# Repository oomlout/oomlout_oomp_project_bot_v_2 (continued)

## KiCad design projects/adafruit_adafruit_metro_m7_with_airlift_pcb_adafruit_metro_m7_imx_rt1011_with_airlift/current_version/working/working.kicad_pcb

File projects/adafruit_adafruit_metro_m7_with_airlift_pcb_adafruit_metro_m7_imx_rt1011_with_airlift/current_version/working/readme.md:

# adafruit_metro_m7_with_airlift_pcb
 
## summary 
* id: adafruit_adafruit_metro_m7_with_airlift_pcb_adafruit_metro_m7_imx_rt1011_with_airlift
* user: adafruit
* name: adafruit_metro_m7_with_airlift_pcb
* board: adafruit_metro_m7_imx_rt1011_with_airlift
* repo: https://github.com/adafruit/Adafruit-Metro-M7-with-AirLift-PCB

* src_file_repo_sch: 
* src_file_repo_sch_link: https://github.com/adafruit/Adafruit-Metro-M7-with-AirLift-PCB/tree/main/
* full details link: https://github.com/oomlout/oomlout_oomp_project_bot_v_2/tree/main/projects/adafruit_adafruit_metro_m7_with_airlift_pcb_adafruit_metro_m7_imx_rt1011_with_airlift/current_version/working  

## schematic  
  
[schematic (pdf)](working_schematic.pdf) 

## pcb  

[board (pdf)](working.pdf)  

## working_bom
| Id | Designator | Footprint | Quantity | Designation | Supplier and ref |  | None | 
| --- | --- | --- | --- | --- | --- | --- | --- | 
| 1 | U$18 | METROM7_RT1011AIR_TOP | 1 |  |  |  | [''] | 
| 2 | R5,R13,R7,R12,R15,R9,R10 | 0603-NO | 7 | 10K |  |  | [''] | 
| 3 | R11,R17,R8,R3,R14,R2 | 0603-NO | 6 | 5.1K |  |  | [''] | 
| 4 | X2 | 2X05_1.27MM_BOX_POSTS | 1 | 2x5 0.05 SWD" |  |  | [''] | 
| 5 | C46,C40,C47,C21,C39,C19,C31,C20,C2,C55,C18,C51,C3,C5,C48,C45 | 0805-NO | 16 | 10uF |  |  | [''] | 
| 6 | D1 | SOD-123 | 1 | MBR120 |  |  | [''] | 
| 7 | C58,C33,C50,C53,C57,C52,C38,C56,C49 | 0603-NO | 9 | 0.22uF |  |  | [''] | 
| 8 | U3 | SOIC8_208MIL | 1 | W25Q64JV |  |  | [''] | 
| 9 | TR1,T2 | SOT-23 | 2 | DMP3098L-7 |  |  | [''] | 
| 10 | FD2,FD3,FD1 | FIDUCIAL_1MM | 3 | FIDUCIAL_1MM |  |  | [''] | 
| 11 | @HOLE3,@HOLE0,@HOLE1,@HOLE2 |  | 4 |  |  |  | [''] | 
| 12 | JP1 | 1X01_ROUND | 1 |  |  |  | [''] | 
| 13 | IC4 | SOT23-WIDE | 1 | RESET_SUPERVISORAPX80X_SA |  |  | [''] | 
| 14 | C26,C25 | 0603-NO | 2 | 16pF |  |  | [''] | 
| 15 | LED1 | LED3535_FULLPADS | 1 | WS2812B_3535FULL |  |  | [''] | 
| 16 | C34 | 0805-NO | 1 | 22uF |  |  | [''] | 
| 17 | PC1,PC2 | PANASONIC_D | 2 | 47uF/25V |  |  | [''] | 
| 18 | IC1 | SOT23-5L | 1 | 74AHC1G125 |  |  | [''] | 
| 19 | C6,C12,C37,C13,C35,C41,C43,C22,C32,C7 | 0603-NO | 10 | 0.1uF |  |  | [''] | 
| 20 | U$11 | PCBFEAT-REV-040 | 1 |  |  |  | [''] | 
| 21 | R16,R1 | 0603-NO | 2 | 100K |  |  | [''] | 
| 22 | R4 | 0603-NO | 1 | 2.2M |  |  | [''] | 
| 23 | C30,C54,C36,C42,C44,C29 | 0603-NO | 6 | 1uF |  |  | [''] | 
| 24 | POWER0,IOL0 | 1X08_OVALWAVE | 2 | 1x8F |  |  | [''] | 
| 25 | L2 | INDUCTOR_1007 | 1 | 4.7uH |  |  | [''] | 
| 26 | Y1 | CRYSTAL_2.5X2 | 1 | 24MHz 10pF |  |  | [''] | 
| 27 | IOH0 | 1X10_OVALWAVE | 1 | 1x10F |  |  | [''] | 
| 28 | X5 | DCJACK_2MM_PTH | 1 | 2.1mm |  |  | [''] | 
| 29 | R6 | 0603-NO | 1 | 30K |  |  | [''] | 
| 30 | U1 | SOT223-R | 1 | NCP1117ST50T3G |  |  | [''] | 
| 31 | RESET0 | EVQ-Q2_SMALLER | 1 | 6x6mm |  |  | [''] | 
| 32 | L0 | CHIPLED_0603_NOOUTLINE | 1 | RED |  |  | [''] | 
| 33 | X4 | USB_C_CUSB31-CFM2AX-01-X | 1 | USB C |  |  | [''] | 
| 34 | ICSP0 | 2X03_ROUND_70MIL | 1 | 2x3M |  |  | [''] | 
| 35 | ECC1 | SOIC8 | 1 | ATECC108 |  |  | [''] | 
| 36 | AD0 | 1X06_OVALWAVE | 1 | 1x6F |  |  | [''] | 
| 37 | F2 | R1206 | 1 | FUSE |  |  | [''] | 
| 38 | ON0 | CHIPLED_0603_NOOUTLINE | 1 | GREEN |  |  | [''] | 
| 39 | U2 | SOT23-DBV | 1 | AP2112K-3.3 |  |  | [''] | 
| 40 | CONN1 | JST_SH4 | 1 | STEMMA_I2C_QT |  |  | [''] | 
| 41 | X6 | WROOM32 | 1 | ESP32_WROOM32 |  |  | [''] | 
| 42 | SW2 | DIPSWITCH_2PIN | 1 | DIP2 |  |  | [''] | 
| 43 | IC2 | QFP50P1400X1400X160-80N | 1 | IMX_RT1010 |  |  | [''] | 
| 44 | SW1 | SPDT_SMT_SSSS811101 | 1 | SPDT_RA |  |  | [''] | 
| 45 | U$12 | METROM7_RT1011AIR_BOT | 1 |  |  |  | [''] | 
| 46 | TP2,TP1 | TESTPOINT_ROUND_1.5MM | 2 |  |  |  | [''] | 

## bom_schematic
| Ref | Qnty | Value | Cmp name | Footprint | Description | Vendor | DNP | 
| --- | --- | --- | --- | --- | --- | --- | --- | 
| AD0 | 1 | 1x6F | HEADER-1X6OVALWAVE | working:1X06_OVALWAVE |  |  |  | 
| C2, C3, C5, C18, C19, C20, C21, C31, C39, C40, C45, C46, C47, C48, C51, C55 | 16 | 10uF | CAP_CERAMIC0805-NOOUTLINE | working:0805-NO |  |  |  | 
| C6, C7, C12, C13, C22, C32, C35, C37, C41, C43 | 10 | 0.1uF | CAP_CERAMIC0603_NO | working:0603-NO |  |  |  | 
| C25, C26 | 2 | 16pF | CAP_CERAMIC0603_NO | working:0603-NO |  |  |  | 
| C29, C30, C36, C42, C44, C54 | 6 | 1uF | CAP_CERAMIC0603_NO | working:0603-NO |  |  |  | 
| C33, C38, C49, C50, C52, C53, C56, C57, C58 | 9 | 0.22uF | CAP_CERAMIC0603_NO | working:0603-NO |  |  |  | 
| C34 | 1 | 22uF | CAP_CERAMIC0805-NOOUTLINE | working:0805-NO |  |  |  | 
| CONN1 | 1 | STEMMA_I2C_QT | STEMMA_I2C_QT | working:JST_SH4 |  |  |  | 
| D1 | 1 | MBR120 | DIODE-SCHOTTKYSOD-123 | working:SOD-123 |  |  |  | 
| ECC1 | 1 | ATECC108 | ATECC108 | working:SOIC8 |  |  |  | 
| F2 | 1 | FUSE | PTCFUSE-1206 | working:R1206 |  |  |  | 
| FD1, FD2, FD3 | 3 | FIDUCIAL_1MM | FIDUCIAL_1MM | working:FIDUCIAL_1MM |  |  |  | 
| IC1 | 1 | 74AHC1G125 | 74AHC1G125 | working:SOT23-5L |  |  |  | 
| IC2 | 1 | IMX_RT1010 | IMX_RT1010 | working:QFP50P1400X1400X160-80N |  |  |  | 
| IC4 | 1 | RESET_SUPERVISORAPX80X_SA | RESET_SUPERVISORAPX80X_SA | working:SOT23-WIDE |  |  |  | 
| ICSP0 | 1 | 2x3M | HEADER-2X3 | working:2X03_ROUND_70MIL |  |  |  | 
| IOH0 | 1 | 1x10F | HEADER-1X10OVALWAVE | working:1X10_OVALWAVE |  |  |  | 
| IOL0 | 1 | 1x8F | HEADER-1X8OVALWAVE | working:1X08_OVALWAVE |  |  |  | 
| JP1 | 1 | HEADER-1X1ROUND | HEADER-1X1ROUND | working:1X01_ROUND |  |  |  | 
| L0 | 1 | RED | LED0603_NOOUTLINE | working:CHIPLED_0603_NOOUTLINE |  |  |  | 
| L2 | 1 | 4.7uH | INDUCTOR | working:INDUCTOR_1007 |  |  |  | 
| LED1 | 1 | WS2812B_3535FULL | WS2812B_3535FULL | working:LED3535_FULLPADS |  |  |  | 
| ON0 | 1 | GREEN | LED0603_NOOUTLINE | working:CHIPLED_0603_NOOUTLINE |  |  |  | 
| PC1, PC2 | 2 | 47uF/25V | CAP_ELECTROLYTICPANASONIC_D | working:PANASONIC_D |  |  |  | 
| POWER0 | 1 | 1x8F | HEADER-1X8OVALWAVE | working:1X08_OVALWAVE |  |  |  | 
| R1, R16 | 2 | 100K | RESISTOR_0603_NOOUT | working:0603-NO |  |  |  | 
| R2, R3, R8, R11, R14, R17 | 6 | 5.1K | RESISTOR_0603_NOOUT | working:0603-NO |  |  |  | 
| R4 | 1 | 2.2M | RESISTOR_0603_NOOUT | working:0603-NO |  |  |  | 
| R5, R7, R9, R10, R12, R13, R15 | 7 | 10K | RESISTOR_0603_NOOUT | working:0603-NO |  |  |  | 
| R6 | 1 | 30K | RESISTOR_0603_NOOUT | working:0603-NO |  |  |  | 
| RESET0 | 1 | 6x6mm | SWITCH_TACT_SMT_EVQQ2_SMALL | working:EVQ-Q2_SMALLER |  |  |  | 
| SW1 | 1 | SPDT_RA | SWITCH_SPDT | working:SPDT_SMT_SSSS811101 |  |  |  | 
| SW2 | 1 | DIP2 | DIPSWITCH_2PIN | working:DIPSWITCH_2PIN |  |  |  | 
| T2 | 1 | DMP3098L-7 | PMOSSOT23 | working:SOT-23 |  |  |  | 
| TP1, TP2 | 2 | TESTPOINTROUND1.5MM | TESTPOINTROUND1.5MM | working:TESTPOINT_ROUND_1.5MM |  |  |  | 
| TR1 | 1 | DMP3098L-7 | 0297_PMV48XP | working:SOT-23 |  |  |  | 
| U1 | 1 | NCP1117ST50T3G | LM1117SOT223-REFLOW | working:SOT223-R |  |  |  | 
| U2 | 1 | LP2985-XXDBVR | LP2985-XXDBVR | working:SOT23-DBV |  |  |  | 
| U3 | 1 | W25Q64JV | SPIFLASH_8PIN208MIL | working:SOIC8_208MIL |  |  |  | 
| X2 | 1 | 2x5 0.05" SWD | JTAG-CORTEXBOXPOSTS | working:2X05_1.27MM_BOX_POSTS |  |  |  | 
| X4 | 1 | USB C | USB_C | working:USB_C_CUSB31-CFM2AX-01-X |  |  |  | 
| X5 | 1 | 2.1mm | DCBARRELPTH | working:DCJACK_2MM_PTH |  |  |  | 
| X6 | 1 | ESP32_WROOM32 | ESP32_WROOM32 | working:WROOM32 |  |  |  | 
| Y1 | 1 | 24MHz 10pF | CRYSTAL2.5X2.0 | working:CRYSTAL_2.5X2 |  |  |  |

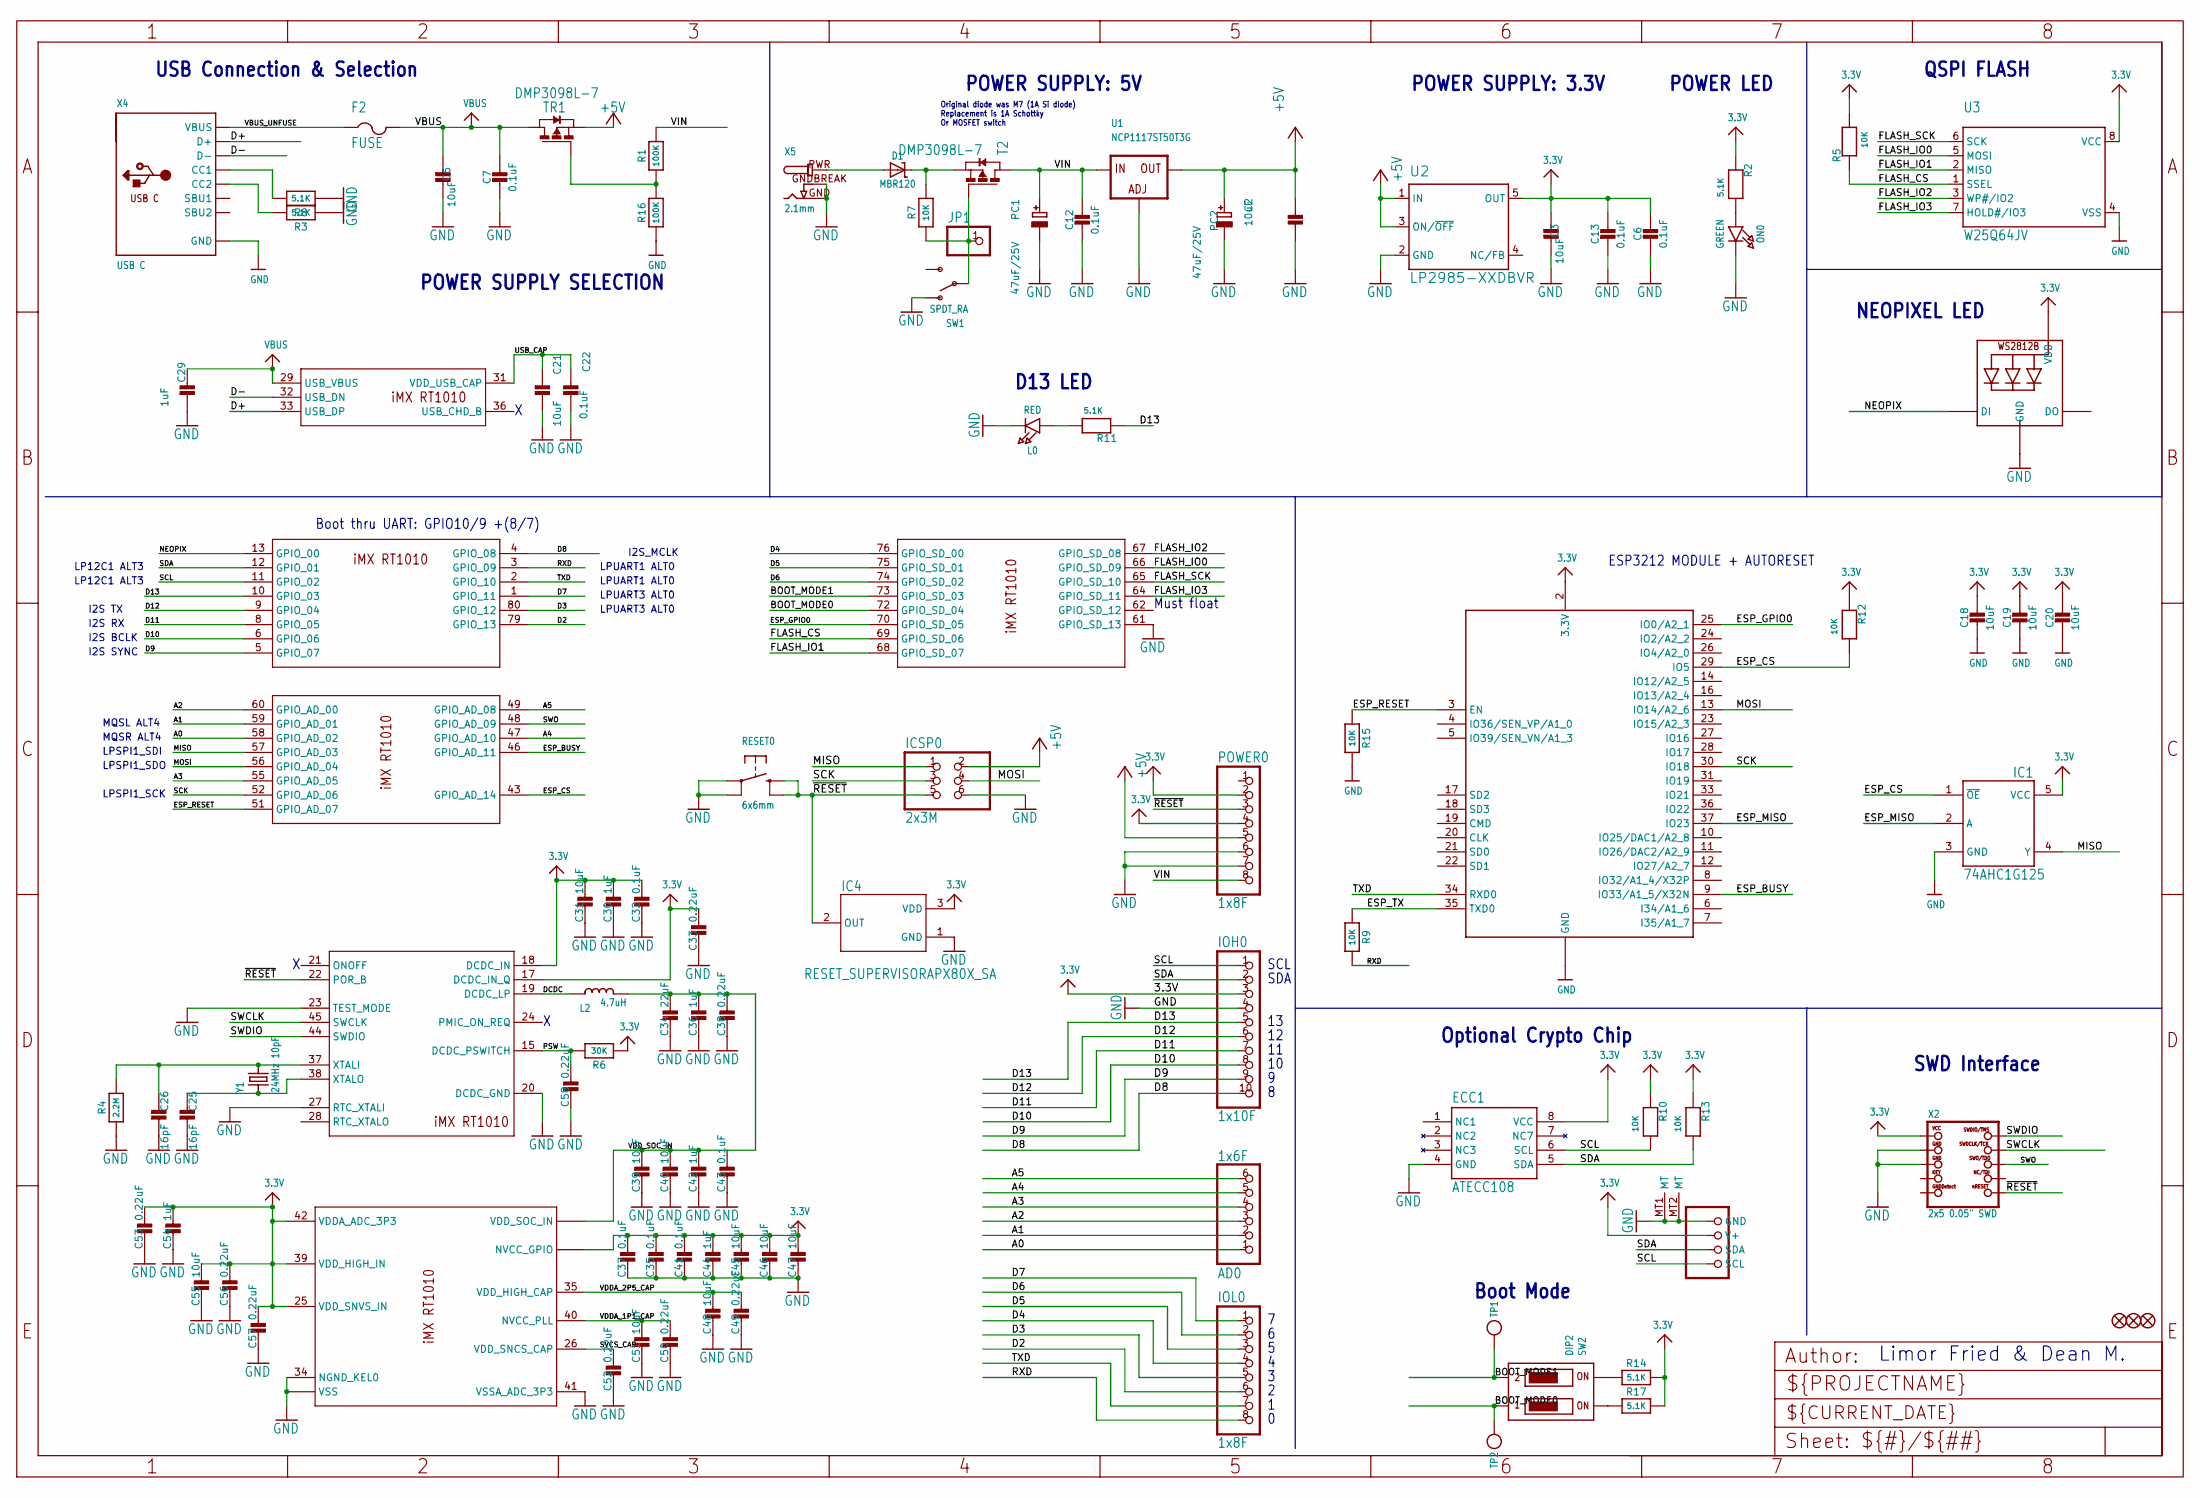
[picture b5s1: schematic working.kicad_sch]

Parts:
AD0: 1x6F; 1X06_OVALWAVE
C2, C3, C5, C18, C19, C20, C21, C31, C39, C40, C45, C46, C47, C48, C51, C55: 10uF; 0805-NO
C6, C7, C12, C13, C22, C32, C35, C37, C41, C43: 0.1uF; 0603-NO
C25, C26: 16pF; 0603-NO
C29, C30, C36, C42, C44, C54: 1uF; 0603-NO
C33, C38, C49, C50, C52, C53, C56, C57, C58: 0.22uF; 0603-NO
C34: 22uF; 0805-NO
CONN1: STEMMA_I2C_QT; JST_SH4
D1: MBR120; SOD-123
ECC1: ATECC108; SOIC8
F2: FUSE; R1206
FD1, FD2, FD3: FIDUCIAL_1MM
IC1: 74AHC1G125; SOT23-5L
IC2: IMX_RT1010; QFP50P1400X1400X160-80N
IC4: RESET_SUPERVISORAPX80X_SA; SOT23-WIDE
ICSP0: 2x3M; 2X03_ROUND_70MIL
IOH0: 1x10F; 1X10_OVALWAVE
IOL0: 1x8F; 1X08_OVALWAVE
JP1: HEADER-1X1ROUND; 1X01_ROUND
L0: RED; CHIPLED_0603_NOOUTLINE
L2: 4.7uH; INDUCTOR_1007
LED1: WS2812B_3535FULL; LED3535_FULLPADS
ON0: GREEN; CHIPLED_0603_NOOUTLINE
PC1, PC2: 47uF/25V; PANASONIC_D
POWER0: 1x8F; 1X08_OVALWAVE
R1, R16: 100K; 0603-NO
R2, R3, R8, R11, R14, R17: 5.1K; 0603-NO
R4: 2.2M; 0603-NO
R5, R7, R9, R10, R12, R13, R15: 10K; 0603-NO
R6: 30K; 0603-NO
RESET0: 6x6mm; EVQ-Q2_SMALLER
SW1: SPDT_RA; SPDT_SMT_SSSS811101
SW2: DIP2; DIPSWITCH_2PIN
T2: DMP3098L-7; SOT-23
TP1, TP2: TESTPOINTROUND1.5MM; TESTPOINT_ROUND_1.5MM
TR1: DMP3098L-7; SOT-23
U1: NCP1117ST50T3G; SOT223-R
U2: LP2985-XXDBVR; SOT23-DBV
U3: W25Q64JV; SOIC8_208MIL
X2: 2x5 0.05" SWD; 2X05_1.27MM_BOX_POSTS
X4: USB C; USB_C_CUSB31-CFM2AX-01-X
X5: 2.1mm; DCJACK_2MM_PTH
X6: ESP32_WROOM32; WROOM32
Y1: 24MHz 10pF; CRYSTAL_2.5X2

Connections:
3.3V: C3.2, C6.2, C13.1, C18.1, C19.1, C20.1, C30.1, C31.1, C32.1, C33.1, C35.1, C37.1, C41.1, C44.1, C45.1, C46.1, C47.1, C53.1, C54.1, C55.1, C56.1, C57.1, CONN1.2 (V+), ECC1.8 (VCC), IC1.5 (VCC), IC2.7 (NVCC_GPIO), IC2.17 (DCDC_IN_Q), IC2.18 (DCDC_IN), IC2.25 (VDD_SNVS_IN), IC2.39 (VDD_HIGH_IN), IC2.42 (VDDA_ADC_3P3), IC2.50 (NVCC_GPIO), IC2.63 (NVCC_GPIO), IC2.71 (NVCC_GPIO), IC4.3 (VDD), IOH0.3, LED1.2 (VDD), POWER0.2, POWER0.4, R2.1, R5.2, R6.1, R10.1, R12.1, R13.1, R14.2, R17.2, U2.5 (OUT), U3.8 (VCC), X2.1 (VCC), X6.2 (3.3V)
+5V: C2.2, ICSP0.2, PC2.+, POWER0.5, TR1.2 (S), U1.2 (OUT), U1.4 (OUT), U2.1 (IN), U2.3 (ON/~OFF)
A0: AD0.1, IC2.58 (GPIO_AD_02)
A1: AD0.2, IC2.59 (GPIO_AD_01)
A2: AD0.3, IC2.60 (GPIO_AD_00)
A3: AD0.4, IC2.55 (GPIO_AD_05)
A4: AD0.5, IC2.47 (GPIO_AD_10)
A5: AD0.6, IC2.49 (GPIO_AD_08)
BOOT_MODE0: IC2.72 (GPIO_SD_04), SW2.1OFF, TP2.P$1
BOOT_MODE1: IC2.73 (GPIO_SD_03), SW2.2OFF, TP1.P$1
D2: IC2.79 (GPIO_13), IOL0.6
D3: IC2.80 (GPIO_12), IOL0.5
D4: IC2.76 (GPIO_SD_00), IOL0.4
D5: IC2.75 (GPIO_SD_01), IOL0.3
D6: IC2.74 (GPIO_SD_02), IOL0.2
D7: IC2.1 (GPIO_11), IOL0.1
D8: IC2.4 (GPIO_08), IOH0.10
D9: IC2.5 (GPIO_07), IOH0.9
D10: IC2.6 (GPIO_06), IOH0.8
D11: IC2.8 (GPIO_05), IOH0.7
D12: IC2.9 (GPIO_04), IOH0.6
D13: IC2.10 (GPIO_03), IOH0.5, R11.1
D+: IC2.33 (USB_DP), X4.A6 (D+), X4.B6 (D+)
D-: IC2.32 (USB_DN), X4.A7 (D-), X4.B7 (D-)
DCDC: IC2.19 (DCDC_LP), L2.P$1 (1)
ESP_BUSY: IC2.46 (GPIO_AD_11), X6.9 (IO33/A1_5/X32N)
ESP_CS: IC1.1 (~OE), IC2.43 (GPIO_AD_14), R12.2, X6.29 (IO5)
ESP_GPIO0: IC2.70 (GPIO_SD_05), X6.25 (IO0/A2_1)
ESP_MISO: IC1.2 (A), X6.37 (IO23)
ESP_RESET: IC2.51 (GPIO_AD_07), R15.1, X6.3 (EN)
ESP_TX: R9.1, X6.35 (TXD0)
FLASH_CS: IC2.69 (GPIO_SD_06), R5.1, U3.1 (SSEL)
FLASH_IO0: IC2.66 (GPIO_SD_09), U3.5 (MOSI)
FLASH_IO1: IC2.68 (GPIO_SD_07), U3.2 (MISO)
FLASH_IO2: IC2.67 (GPIO_SD_08), U3.3 (WP#/IO2)
FLASH_IO3: IC2.64 (GPIO_SD_11), U3.7 (HOLD#/IO3)
FLASH_SCK: IC2.65 (GPIO_SD_10), U3.6 (SCK)
GND: C2.1, C3.1, C5.1, C6.1, C7.2, C12.2, C13.2, C18.2, C19.2, C20.2, C21.1, C22.2, C25.2, C26.2, C29.2, C30.2, C31.2, C32.2, C33.2, C34.2, C35.2, C36.2, C37.2, C38.2, C39.2, C40.2, C41.2, C42.2, C43.2, C44.2, C45.2, C46.2, C47.2, C48.2, C49.2, C50.2, C51.2, C52.2, C53.2, C54.2, C55.2, C56.2, C57.2, C58.2, CONN1.1 (GND), CONN1.MT1 (MT), CONN1.MT2 (MT), ECC1.4 (GND), IC1.3 (GND), IC2.16 (VSS), IC2.20 (DCDC_GND), IC2.23 (TEST_MODE), IC2.27 (RTC_XTALI), IC2.30 (VSS), IC2.34 (NGND_KEL0), IC2.41 (VSSA_ADC_3P3), IC2.54 (VSS), IC2.61 (GPIO_SD_13), IC2.78 (VSS), IC4.1 (GND), ICSP0.6, IOH0.4, L0.C, LED1.4 (GND), ON0.C, PC1.-, PC2.-, POWER0.6, POWER0.7, R3.1, R4.1, R8.1, R15.2, R16.1, RESET0.A, RESET0.A' (P1), SW1.A (O), U1.1 (ADJ), U2.2 (GND), U3.4 (VSS)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
MISO: IC1.4 (Y), IC2.57 (GPIO_AD_03), ICSP0.1
MOSI: IC2.56 (GPIO_AD_04), ICSP0.4, X6.13 (IO14/A2_6)
unnamed: L0.A, R11.2
unnamed: ON0.A, R2.2
unnamed: R14.1, SW2.2ON
unnamed: R17.1, SW2.1ON
unnamed: R8.2, X4.A5 (CC1)
unnamed: R3.2, X4.B5 (CC2)
unnamed: C26.1, IC2.37 (XTALI), R4.2, Y1.3 (2)
unnamed: C25.1, IC2.38 (XTALO), Y1.1
unnamed: R1.1, R16.2, TR1.3 (G)
unnamed: D1.C, R7.2, T2.2 (S)
NEOPIX: IC2.13 (GPIO_00), LED1.1 (DI)
PSW: C58.1, IC2.15 (DCDC_PSWITCH), R6.2
PWRIN: D1.A, X5.PWR
PWR_SWITCH: JP1.1, R7.1, SW1.B, T2.3 (G)
RXD: IC2.3 (GPIO_09), IOL0.8, R9.2
SCK: IC2.52 (GPIO_AD_06), ICSP0.3, X6.30 (IO18)
SCL: CONN1.4 (SCL), ECC1.6 (SCL), IC2.11 (GPIO_02), IOH0.1, R10.2
SDA: CONN1.3 (SDA), ECC1.5 (SDA), IC2.12 (GPIO_01), IOH0.2, R13.2
SVCS_CAP: C52.1, IC2.26 (VDD_SNCS_CAP)
SWCLK: IC2.45 (SWCLK), X2.4 (SWDCLK)
SWDIO: IC2.44 (SWDIO), X2.2 (SWDIO)
SWO: IC2.48 (GPIO_AD_09), X2.6 (SWO)
TXD: IC2.2 (GPIO_10), IOL0.7, X6.34 (RXD0)
USB_CAP: C21.2, C22.1, IC2.31 (VDD_USB_CAP)
VBUS: C5.2, C7.1, C29.1, F2.2, IC2.29 (USB_VBUS), TR1.1 (D)
VBUS_UNFUSE: F2.1, X4.A4B9 (VBUS), X4.B4A9 (VBUS)
VDDA_1P1_CAP: C50.1, C51.1, IC2.40 (NVCC_PLL)
VDDA_2P5_CAP: C48.1, C49.1, IC2.35 (VDD_HIGH_CAP)
VDD_SOC_IN: C34.1, C36.1, C38.1, C39.1, C40.1, C42.1, C43.1, IC2.14 (VDD_SOC_IN), IC2.53 (VDD_SOC_IN), IC2.77 (VDD_SOC_IN), L2.P$2 (2)
VIN: C12.1, PC1.+, POWER0.8, R1.2, T2.1 (D), U1.3 (IN)
~RESET: IC2.22 (POR_B), IC4.2 (OUT), ICSP0.5, POWER0.3, RESET0.B (S), RESET0.B' (S1), X2.10 (NRESET)

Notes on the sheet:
USB Connection & Selection
Optional Crypto Chip
QSPI FLASH
LPUART3 ALT0
NEOPIXEL LED
Boot Mode
MQSR ALT4
POWER SUPPLY: 3.3V
SDA
Boot thru UART: GPIO10/9 +(8/7)
LP12C1 ALT3
POWER LED
LPSPI1_SDO
POWER SUPPLY SELECTION
ESP3212 MODULE + AUTORESET
I2S BCLK
LPSPI1_SDI
I2S RX
Limor Fried & Dean M.
MQSL ALT4
POWER SUPPLY: 5V
D13 LED
SCL
I2S TX
LPSPI1_SCK
LPUART1 ALT0
I2S_MCLK
Original diode was M7 (1A Si diode) Replacement is 1A Schottky Or MOSFET switch
SWD Interface
Must float
I2S SYNC

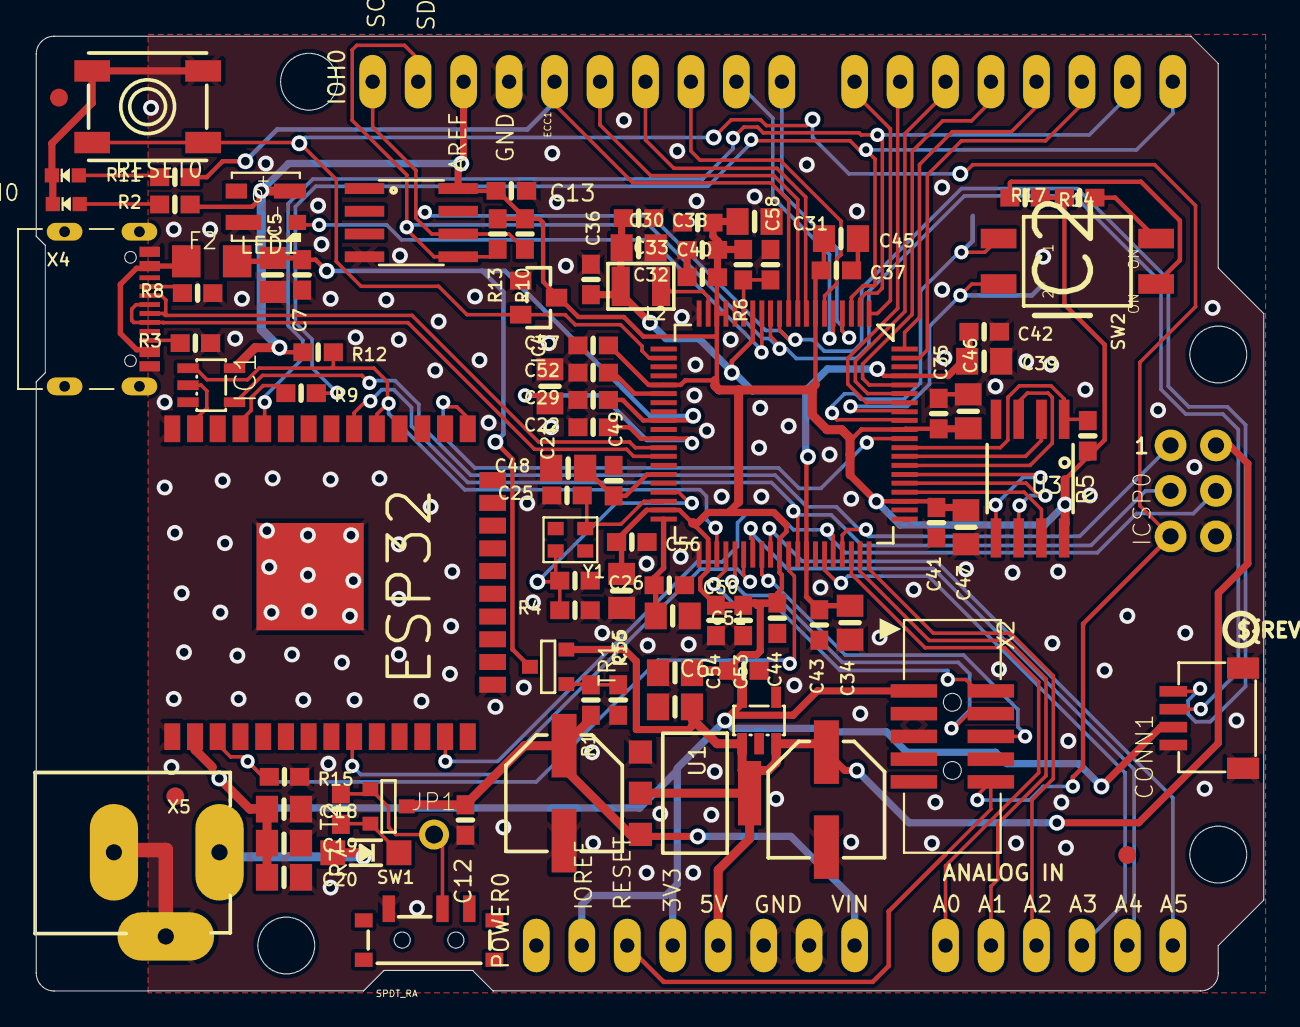
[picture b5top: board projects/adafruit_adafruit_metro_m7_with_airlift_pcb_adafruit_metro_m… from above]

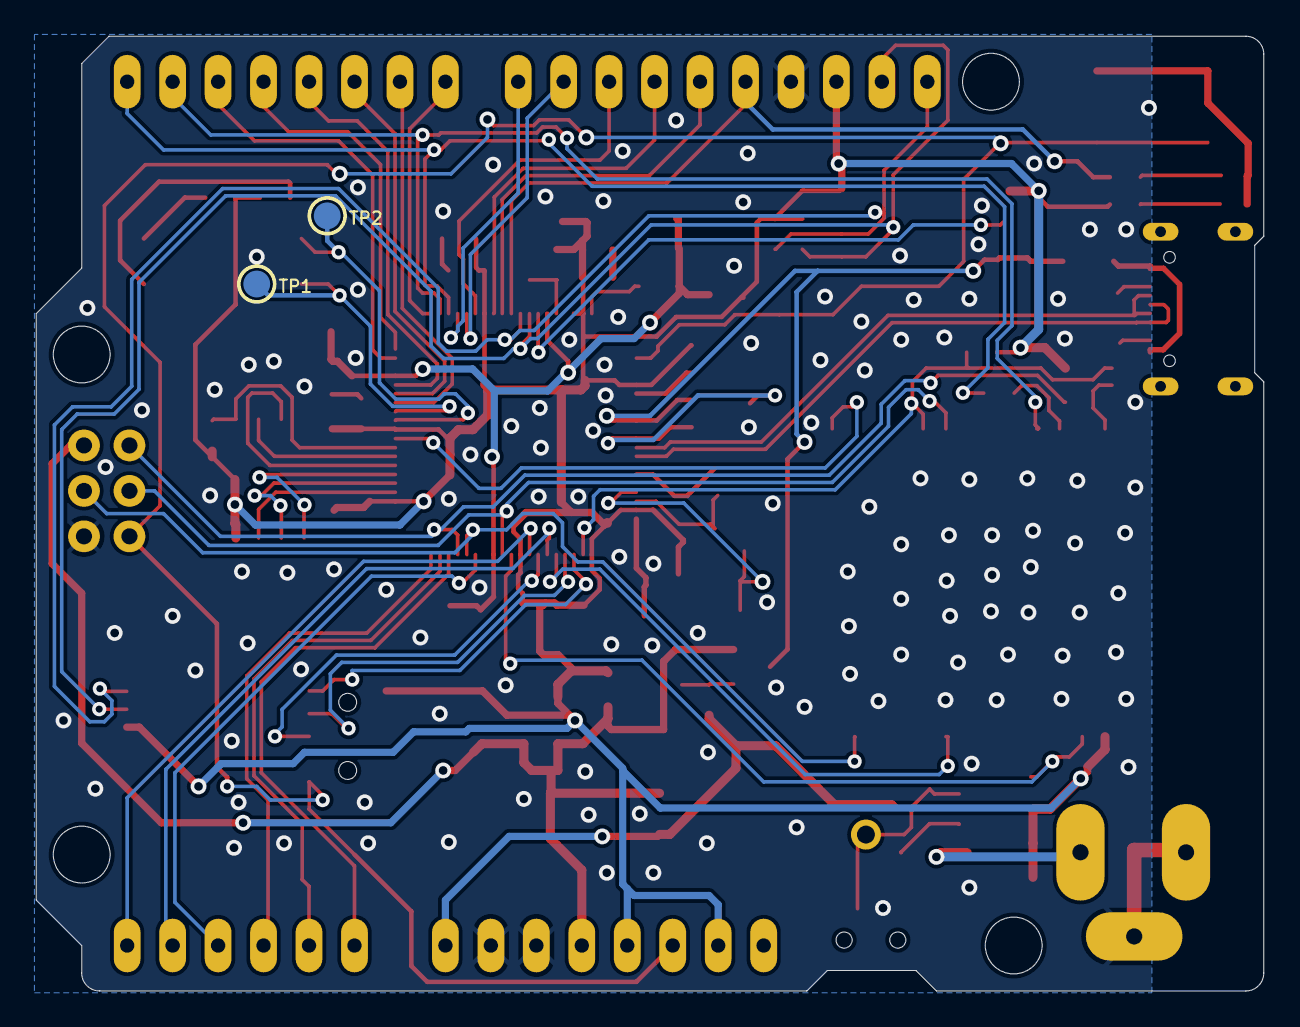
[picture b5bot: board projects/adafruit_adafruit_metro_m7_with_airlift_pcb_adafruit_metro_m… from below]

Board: 2 copper layers, 68.6 x 53.3 mm, 105 parts (3 on the bottom side), 71 nets.

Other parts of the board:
@HOLE0, @HOLE1, @HOLE2, @HOLE3: (no value)
U$11: PCBFEAT-REV-040
U$12: METROM7_RT1011AIR_BOT
U$18: METROM7_RT1011AIR_TOP

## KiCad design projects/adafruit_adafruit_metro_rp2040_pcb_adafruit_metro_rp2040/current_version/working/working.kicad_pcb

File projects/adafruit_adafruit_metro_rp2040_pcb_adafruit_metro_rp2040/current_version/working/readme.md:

# adafruit_metro_rp2040_pcb
 
## summary 
* id: adafruit_adafruit_metro_rp2040_pcb_adafruit_metro_rp2040
* user: adafruit
* name: adafruit_metro_rp2040_pcb
* board: adafruit_metro_rp2040
* repo: https://github.com/adafruit/Adafruit-Metro-RP2040-PCB

* src_file_repo_sch: 
* src_file_repo_sch_link: https://github.com/adafruit/Adafruit-Metro-RP2040-PCB/tree/main/
* full details link: https://github.com/oomlout/oomlout_oomp_project_bot_v_2/tree/main/projects/adafruit_adafruit_metro_rp2040_pcb_adafruit_metro_rp2040/current_version/working  

## schematic  
  
[schematic (pdf)](working_schematic.pdf) 

## pcb  

[board (pdf)](working.pdf)  

## working_bom
| Id | Designator | Footprint | Quantity | Designation | Supplier and ref |  | None | 
| --- | --- | --- | --- | --- | --- | --- | --- | 
| 1 | JP1 | 1X01_ROUND | 1 |  |  |  | [''] | 
| 2 | ICSP0 | 2X03_ROUND_70MIL | 1 | 3x2 M |  |  | [''] | 
| 3 | R17,R7,R13,R21,R3,R10 | 0603-NO | 6 | 10K |  |  | [''] | 
| 4 | R24,R25 | 0603-NO | 2 | 22 ohm |  |  | [''] | 
| 5 | FD2,FD1,FD3 | FIDUCIAL_1MM | 3 | FIDUCIAL_1MM |  |  | [''] | 
| 6 | C3,C20,C18,C2,C19,C5 | 0805-NO | 6 | 10uF |  |  | [''] | 
| 7 | DEBUG0 | JST_SH3 | 1 | JST_SH3 |  |  | [''] | 
| 8 | SW4 | EG1390 | 1 | DPDT |  |  | [''] | 
| 9 | C11,C16,C28 | 0603-NO | 3 | 1uF |  |  | [''] | 
| 10 | U$11 | PCBFEAT-REV-040 | 1 |  |  |  | [''] | 
| 11 | D1 | SOD-123 | 1 | MBR120 |  |  | [''] | 
| 12 | @HOLE1,@HOLE2,@HOLE0,@HOLE3 |  | 4 |  |  |  | [''] | 
| 13 | CONN1 | JST_SH4 | 1 | STEMMA_I2C_QT |  |  | [''] | 
| 14 | R2,R20,R19,R11 | 0603-NO | 4 | 5.1K |  |  | [''] | 
| 15 | SW2,SW3 | SPST_TACTILE_RA | 2 | SW_RA |  |  | [''] | 
| 16 | POWER0,IOL0 | 1X08_OVALWAVE | 2 | 20610 |  |  | [''] | 
| 17 | C15,C7,C17,C24,C13,C6,C12,C25,C23,C21,C22,C14,C10 | 0603-NO | 13 | 0.1uF |  |  | [''] | 
| 18 | ON0 | CHIPLED_0603_NOOUTLINE | 1 | GREEN |  |  | [''] | 
| 19 | U2 | SOT23-DBV | 1 | AP2112K-3.3 |  |  | [''] | 
| 20 | U1 | SOT223-R | 1 | NCP1117ST50T3G |  |  | [''] | 
| 21 | C26,C27 | 0603-NO | 2 | 22pF |  |  | [''] | 
| 22 | T2,TR1 | SOT23-WIDE | 2 | DMP3098L |  |  | [''] | 
| 23 | R1,R16 | 0603-NO | 2 | 100K |  |  | [''] | 
| 24 | X5 | DCJACK_2MM_PTH | 1 | 2.1mm |  |  | [''] | 
| 25 | SW1 | SPDT_SMT_SSSS811101 | 1 | SPDT_RA |  |  | [''] | 
| 26 | F2 | R1206 | 1 | FUSE |  |  | [''] | 
| 27 | LED2 | LED3535_FULLPADS | 1 | WS2812B_3535FULL |  |  | [''] | 
| 28 | Y1 | CRYSTAL_2.5X2 | 1 | 12MHz_12pF |  |  | [''] | 
| 29 | IC2 | QFN56_7MM_REDUCEDEPAD | 1 | RP2040_QFN56 |  |  | [''] | 
| 30 | SWD0 | 2X05_1.27MM_BOX_POSTS | 1 | 2x5_0.5IN |  |  | [''] | 
| 31 | PC2,PC1 | PANASONIC_D | 2 | 47uF/25V |  |  | [''] | 
| 32 | R23,R26 | 0603-NO | 2 | 1K |  |  | [''] | 
| 33 | U$29 | METRO_RP2040_TOP | 1 |  |  |  | [''] | 
| 34 | L0 | CHIPLED_0603_NOOUTLINE | 1 | RED |  |  | [''] | 
| 35 | AD0 | 1X06_OVALWAVE | 1 | 20609 |  |  | [''] | 
| 36 | U6 | SOIC8_208MIL | 1 | W25Q128 |  |  | [''] | 
| 37 | X1 | MICROSD | 1 | MICROSD |  |  | [''] | 
| 38 | X3 | USB_C_CUSB31-CFM2AX-01-X | 1 | USB Type C |  |  | [''] | 
| 39 | IOH0 | 1X10_OVALWAVE | 1 | 20611 |  |  | [''] | 
| 40 | U$15 | METRO_RP2040_BOT | 1 |  |  |  | [''] | 
| 41 | D+1,D-1 | B1,27 | 2 | TPB1,27 |  |  | [''] | 
| 42 | TP1 | TESTPOINT_ROUND_1.5MM_NO | 1 |  |  |  | [''] | 

## bom_schematic
| Ref | Qnty | Value | Cmp name | Footprint | Description | Vendor | DNP | 
| --- | --- | --- | --- | --- | --- | --- | --- | 
| AD0 | 1 | 20609 | HEADER-1X6OVALWAVE | working:1X06_OVALWAVE |  |  |  | 
| C2, C3, C5, C18, C19, C20 | 6 | 10uF | CAP_CERAMIC0805-NOOUTLINE | working:0805-NO |  |  |  | 
| C6, C7, C10, C12, C13, C14, C15, C17, C21, C22, C23, C24, C25 | 13 | 0.1uF | CAP_CERAMIC0603_NO | working:0603-NO |  |  |  | 
| C11, C16, C28 | 3 | 1uF | CAP_CERAMIC0603_NO | working:0603-NO |  |  |  | 
| C26, C27 | 2 | 22pF | CAP_CERAMIC0603_NO | working:0603-NO |  |  |  | 
| CONN1 | 1 | STEMMA_I2C_QT | STEMMA_I2C_QT | working:JST_SH4 |  |  |  | 
| D1 | 1 | MBR120 | DIODE-SCHOTTKYSOD-123 | working:SOD-123 |  |  |  | 
| D+1 | 1 | TPB1,27 | TPB1,27 | working:B1,27 |  |  |  | 
| D-1 | 1 | TPB1,27 | TPB1,27 | working:B1,27 |  |  |  | 
| DEBUG0 | 1 | JST_SH3 | CON_JST_SH_3PINSH | working:JST_SH3 |  |  |  | 
| F2 | 1 | FUSE | PTCFUSE-1206 | working:R1206 |  |  |  | 
| FD1, FD2, FD3 | 3 | FIDUCIAL_1MM | FIDUCIAL_1MM | working:FIDUCIAL_1MM |  |  |  | 
| IC2 | 1 | RP2040_QFN56 | RP2040_QFN56 | working:QFN56_7MM_REDUCEDEPAD |  |  |  | 
| ICSP0 | 1 | 3x2 M | HEADER-2X3 | working:2X03_ROUND_70MIL |  |  |  | 
| IOH0 | 1 | 20611 | HEADER-1X10OVALWAVE | working:1X10_OVALWAVE |  |  |  | 
| IOL0 | 1 | 20610 | HEADER-1X8OVALWAVE | working:1X08_OVALWAVE |  |  |  | 
| JP1 | 1 | HEADER-1X1ROUND | HEADER-1X1ROUND | working:1X01_ROUND |  |  |  | 
| L0 | 1 | RED | LED0603_NOOUTLINE | working:CHIPLED_0603_NOOUTLINE |  |  |  | 
| LED2 | 1 | WS2812B_3535FULL | WS2812B_3535FULL | working:LED3535_FULLPADS |  |  |  | 
| ON0 | 1 | GREEN | LED0603_NOOUTLINE | working:CHIPLED_0603_NOOUTLINE |  |  |  | 
| PC1, PC2 | 2 | 47uF/25V | CAP_ELECTROLYTICPANASONIC_D | working:PANASONIC_D |  |  |  | 
| POWER0 | 1 | 20610 | HEADER-1X8OVALWAVE | working:1X08_OVALWAVE |  |  |  | 
| R1, R16 | 2 | 100K | RESISTOR_0603_NOOUT | working:0603-NO |  |  |  | 
| R2, R11, R19, R20 | 4 | 5.1K | RESISTOR_0603_NOOUT | working:0603-NO |  |  |  | 
| R3, R7, R10, R13, R17, R21 | 6 | 10K | RESISTOR_0603_NOOUT | working:0603-NO |  |  |  | 
| R23, R26 | 2 | 1K | RESISTOR_0603_NOOUT | working:0603-NO |  |  |  | 
| R24, R25 | 2 | 22 ohm | RESISTOR_0603_NOOUT | working:0603-NO |  |  |  | 
| SW1 | 1 | SPDT_RA | SWITCH_SPDT | working:SPDT_SMT_SSSS811101 |  |  |  | 
| SW2, SW3 | 2 | SW_RA | SWITCH_SPST_MNT_TACT_RA | working:SPST_TACTILE_RA |  |  |  | 
| SW4 | 1 | DPDT | SWITCH_DPDTEG1390 | working:EG1390 |  |  |  | 
| SWD0 | 1 | 2x5_0.5IN | JTAG-CORTEXBOXPOSTS | working:2X05_1.27MM_BOX_POSTS |  |  |  | 
| T2 | 1 | DMP3098L | MOSFET-PWIDE | working:SOT23-WIDE |  |  |  | 
| TP1 | 1 | TESTPOINTROUND1.5MMNO | TESTPOINTROUND1.5MMNO | working:TESTPOINT_ROUND_1.5MM_NO |  |  |  | 
| TR1 | 1 | DMP3098L | MOSFET-PWIDE | working:SOT23-WIDE |  |  |  | 
| U1 | 1 | NCP1117ST50T3G | LM1117SOT223-REFLOW | working:SOT223-R |  |  |  | 
| U2 | 1 | LP2985-XXDBVR | LP2985-XXDBVR | working:SOT23-DBV |  |  |  | 
| U6 | 1 | W25Q128 | SPIFLASH_8PIN208MIL | working:SOIC8_208MIL |  |  |  | 
| X1 | 1 | MICROSD | MICROSD | working:MICROSD |  |  |  | 
| X3 | 1 | USB Type C | USB_C | working:USB_C_CUSB31-CFM2AX-01-X |  |  |  | 
| X5 | 1 | 2.1mm | DCBARRELPTH | working:DCJACK_2MM_PTH |  |  |  | 
| Y1 | 1 | 12MHz_12pF | CRYSTAL2.5X2.0 | working:CRYSTAL_2.5X2 |  |  |  |

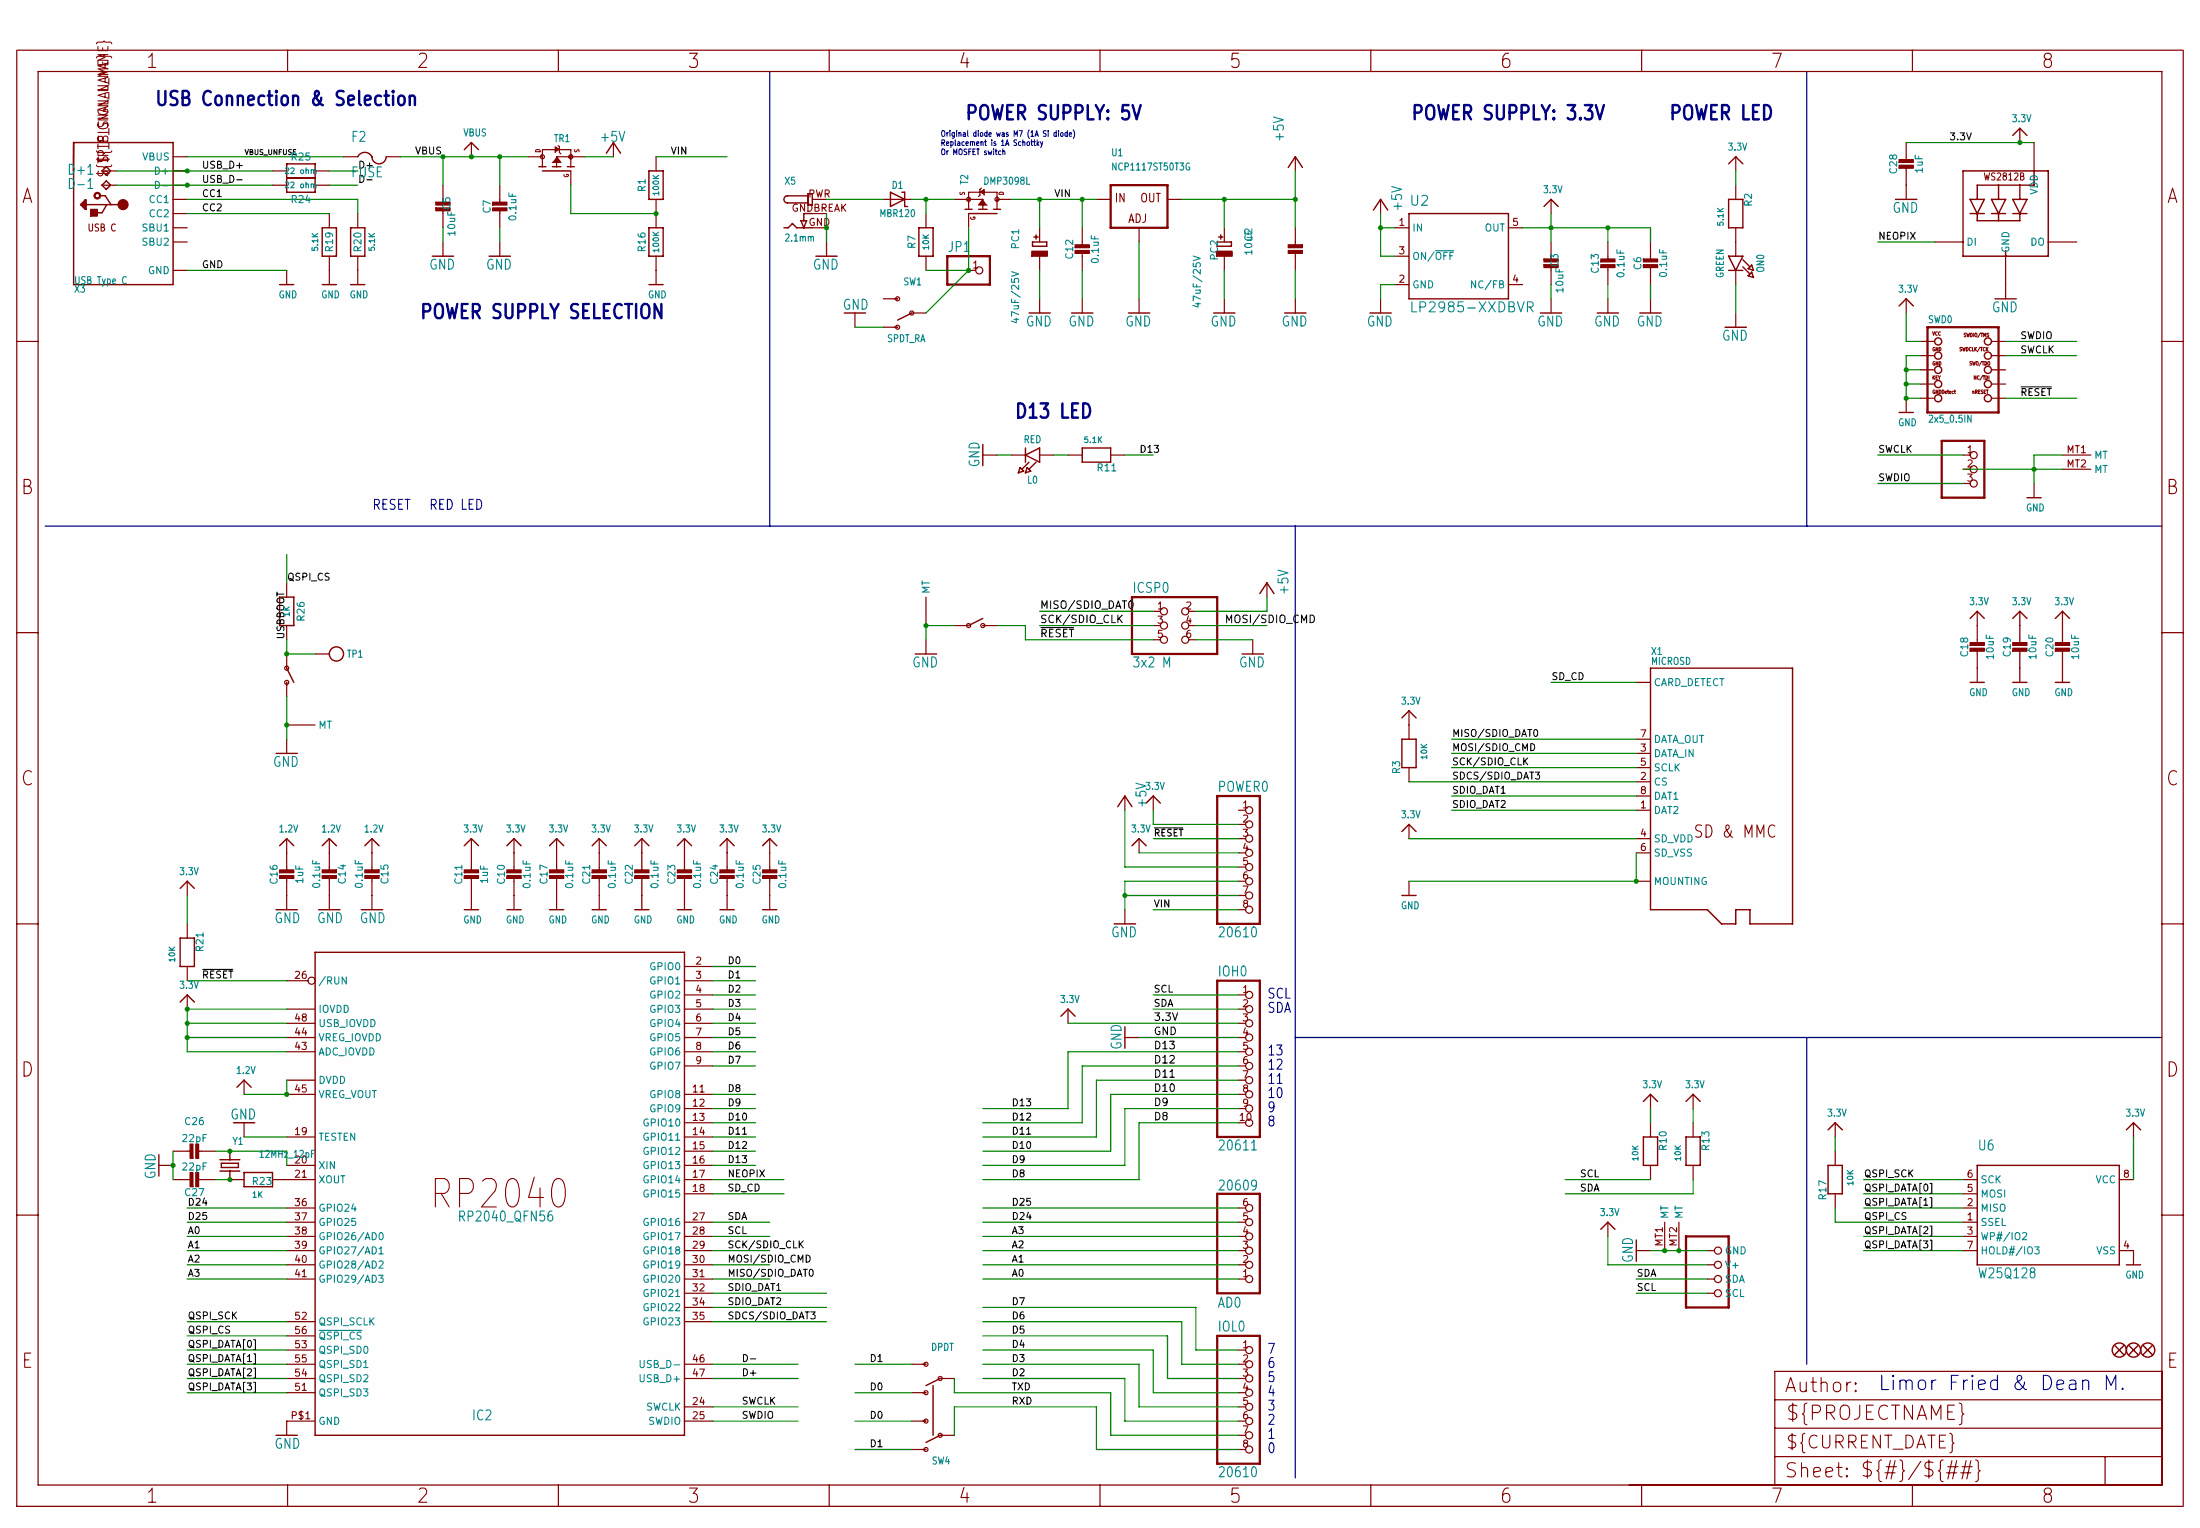
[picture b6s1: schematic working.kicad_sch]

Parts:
AD0: 20609; 1X06_OVALWAVE
C2, C3, C5, C18, C19, C20: 10uF; 0805-NO
C6, C7, C10, C12, C13, C14, C15, C17, C21, C22, C23, C24, C25: 0.1uF; 0603-NO
C11, C16, C28: 1uF; 0603-NO
C26, C27: 22pF; 0603-NO
CONN1: STEMMA_I2C_QT; JST_SH4
D1: MBR120; SOD-123
D+1: TPB1,27; B1,27
D-1: TPB1,27; B1,27
DEBUG0: JST_SH3
F2: FUSE; R1206
FD1, FD2, FD3: FIDUCIAL_1MM
IC2: RP2040_QFN56; QFN56_7MM_REDUCEDEPAD
ICSP0: 3x2 M; 2X03_ROUND_70MIL
IOH0: 20611; 1X10_OVALWAVE
IOL0: 20610; 1X08_OVALWAVE
JP1: HEADER-1X1ROUND; 1X01_ROUND
L0: RED; CHIPLED_0603_NOOUTLINE
LED2: WS2812B_3535FULL; LED3535_FULLPADS
ON0: GREEN; CHIPLED_0603_NOOUTLINE
PC1, PC2: 47uF/25V; PANASONIC_D
POWER0: 20610; 1X08_OVALWAVE
R1, R16: 100K; 0603-NO
R2, R11, R19, R20: 5.1K; 0603-NO
R3, R7, R10, R13, R17, R21: 10K; 0603-NO
R23, R26: 1K; 0603-NO
R24, R25: 22 ohm; 0603-NO
SW1: SPDT_RA; SPDT_SMT_SSSS811101
SW2, SW3: SW_RA; SPST_TACTILE_RA
SW4: DPDT; EG1390
SWD0: 2x5_0.5IN; 2X05_1.27MM_BOX_POSTS
T2: DMP3098L; SOT23-WIDE
TP1: TESTPOINTROUND1.5MMNO; TESTPOINT_ROUND_1.5MM_NO
TR1: DMP3098L; SOT23-WIDE
U1: NCP1117ST50T3G; SOT223-R
U2: LP2985-XXDBVR; SOT23-DBV
U6: W25Q128; SOIC8_208MIL
X1: MICROSD
X3: USB Type C; USB_C_CUSB31-CFM2AX-01-X
X5: 2.1mm; DCJACK_2MM_PTH
Y1: 12MHz_12pF; CRYSTAL_2.5X2

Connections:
1.2V: C14.2, C15.2, C16.1, IC2.23 (DVDD), IC2.45 (VREG_VOUT), IC2.50 (DVDD)
3.3V: C3.2, C6.2, C10.1, C11.1, C13.1, C17.1, C18.1, C19.1, C20.1, C21.1, C22.1, C23.1, C24.1, C25.1, C28.1, CONN1.2 (V+), IC2.1 (IOVDD), IC2.10 (IOVDD), IC2.22 (IOVDD), IC2.33 (IOVDD), IC2.42 (IOVDD), IC2.43 (ADC_IOVDD), IC2.44 (VREG_IOVDD), IC2.48 (USB_IOVDD), IC2.49 (IOVDD), IOH0.3, LED2.2 (VDD), POWER0.2, POWER0.4, R2.1, R3.2, R10.1, R13.1, R17.2, R21.1, SWD0.1 (VCC), U2.5 (OUT), U6.8 (VCC), X1.4 (SD_VDD)
+5V: C2.2, ICSP0.2, PC2.+, POWER0.5, TR1.2 (S), U1.2 (OUT), U1.4 (OUT), U2.1 (IN), U2.3 (ON/~OFF)
A0: AD0.1, IC2.38 (GPIO26/AD0)
A1: AD0.2, IC2.39 (GPIO27/AD1)
A2: AD0.3, IC2.40 (GPIO28/AD2)
A3: AD0.4, IC2.41 (GPIO29/AD3)
CC1: R20.2, X3.A5 (CC1)
CC2: R19.2, X3.B5 (CC2)
D0: IC2.2 (GPIO0), SW4.O2, SW4.S1
D1: IC2.3 (GPIO1), SW4.O1, SW4.S2
D2: IC2.4 (GPIO2), IOL0.6
D3: IC2.5 (GPIO3), IOL0.5
D4: IC2.6 (GPIO4), IOL0.4
D5: IC2.7 (GPIO5), IOL0.3
D6: IC2.8 (GPIO6), IOL0.2
D7: IC2.9 (GPIO7), IOL0.1
D8: IC2.11 (GPIO8), IOH0.10
D9: IC2.12 (GPIO9), IOH0.9
D10: IC2.13 (GPIO10), IOH0.8
D11: IC2.14 (GPIO11), IOH0.7
D12: IC2.15 (GPIO12), IOH0.6
D13: IC2.16 (GPIO13), IOH0.5, R11.1
D24: AD0.5, IC2.36 (GPIO24)
D25: AD0.6, IC2.37 (GPIO25)
D+: IC2.47 (USB_D+), R25.2
D-: IC2.46 (USB_D-), R24.2
GND: C2.1, C3.1, C5.1, C6.1, C7.2, C10.2, C11.2, C12.2, C13.2, C14.1, C15.1, C16.2, C17.2, C18.2, C19.2, C20.2, C21.2, C22.2, C23.2, C24.2, C25.2, C26.1, C27.1, C28.2, CONN1.1 (GND), CONN1.MT1 (MT), CONN1.MT2 (MT), DEBUG0.2, DEBUG0.MT1 (MT), DEBUG0.MT2 (MT), IC2.19 (TESTEN), IC2.P$1 (GND), ICSP0.6, IOH0.4, L0.C, LED2.4 (GND), ON0.C, PC1.-, PC2.-, POWER0.6, POWER0.7, R16.1, R19.1, R20.1, SW1.A (O), SW2.1, SW2.MT1 (MT), SW2.MT2 (MT), SW3.2 (S), SW3.MT1 (MT), SW3.MT2 (MT), SWD0.3 (GND@1), SWD0.5 (GND@2), SWD0.7 (KEY), SWD0.9 (GNDDETECT), U1.1 (ADJ), U2.2 (GND), U6.4 (VSS), X1.6 (SD_VSS), X1.MT1 (MOUNTING), X1.MT2 (MOUNTING), X3.A1B12 (GND), X3.B1A12 (GND), X5.GND, X5.GNDBREAK
MISO/SDIO_DAT0: IC2.31 (GPIO20), ICSP0.1, X1.7 (DATA_OUT)
MOSI/SDIO_CMD: IC2.30 (GPIO19), ICSP0.4, X1.3 (DATA_IN)
unnamed: L0.A, R11.2
unnamed: ON0.A, R2.2
unnamed: C26.2, IC2.20 (XIN), Y1.3 (2)
unnamed: C27.2, R23.1, Y1.1
unnamed: R1.1, R16.2, TR1.1 (G)
unnamed: IC2.21 (XOUT), R23.2
unnamed: D1.C, R7.2, T2.2 (S)
NEOPIX: IC2.17 (GPIO14), LED2.1 (DI)
PWRIN: D1.A, X5.PWR
PWR_SWITCH: JP1.1, R7.1, SW1.B, T2.1 (G)
QSPI_CS: IC2.56 (~QSPI_CS), R17.1, R26.1, U6.1 (SSEL)
QSPI_DATA[0]: IC2.53 (QSPI_SD0), U6.5 (MOSI)
QSPI_DATA[1]: IC2.55 (QSPI_SD1), U6.2 (MISO)
QSPI_DATA[2]: IC2.54 (QSPI_SD2), U6.3 (WP#/IO2)
QSPI_DATA[3]: IC2.51 (QSPI_SD3), U6.7 (HOLD#/IO3)
QSPI_SCK: IC2.52 (QSPI_SCLK), U6.6 (SCK)
RXD: IOL0.8, SW4.P1
SCK/SDIO_CLK: IC2.29 (GPIO18), ICSP0.3, X1.5 (SCLK)
SCL: CONN1.4 (SCL), IC2.28 (GPIO17), IOH0.1, R10.2
SDA: CONN1.3 (SDA), IC2.27 (GPIO16), IOH0.2, R13.2
SDCS/SDIO_DAT3: IC2.35 (GPIO23), R3.1, X1.2 (CS)
SDIO_DAT1: IC2.32 (GPIO21), X1.8 (DAT1)
SDIO_DAT2: IC2.34 (GPIO22), X1.1 (DAT2)
SD_CD: IC2.18 (GPIO15), X1.CD1 (CARD_DETECT), X1.CD2 (CARD_DETECT)
SWCLK: DEBUG0.1, IC2.24 (SWCLK), SWD0.4 (SWDCLK)
SWDIO: DEBUG0.3, IC2.25 (SWDIO), SWD0.2 (SWDIO)
TXD: IOL0.7, SW4.P2
USBBOOT: R26.2, SW3.1, TP1.P$1
USB_D+: D+1.TP, R25.1, X3.A6 (D+), X3.B6 (D+)
USB_D-: D-1.TP, R24.1, X3.A7 (D-), X3.B7 (D-)
VBUS: C5.2, C7.1, F2.2, TR1.3 (D)
VBUS_UNFUSE: F2.1, X3.A4B9 (VBUS), X3.B4A9 (VBUS)
VIN: C12.1, PC1.+, POWER0.8, R1.2, T2.3 (D), U1.3 (IN)
~RESET: IC2.26 (/RUN), ICSP0.5, POWER0.3, R21.2, SW2.2 (S), SWD0.10 (NRESET)

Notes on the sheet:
USB Connection & Selection
RESET
Limor Fried & Dean M.
POWER SUPPLY: 5V
SDA
POWER LED
POWER SUPPLY: 3.3V
RED LED
Original diode was M7 (1A Si diode) Replacement is 1A Schottky Or MOSFET switch
POWER SUPPLY SELECTION
D13 LED
SCL
